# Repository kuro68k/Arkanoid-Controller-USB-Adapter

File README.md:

# Arkanoid-Controller-USB-Adapter

Adapter for the Famicom Arkanoid controller to USB.

Two modes are available, an absolute position mode that is good for Breakout under MAME, and a mouse emulation mode that is better for Arkanoid under MAME.

You need a decent USB port for this. If there is electrical noise it can cause the position to jump. I use a powered hub.

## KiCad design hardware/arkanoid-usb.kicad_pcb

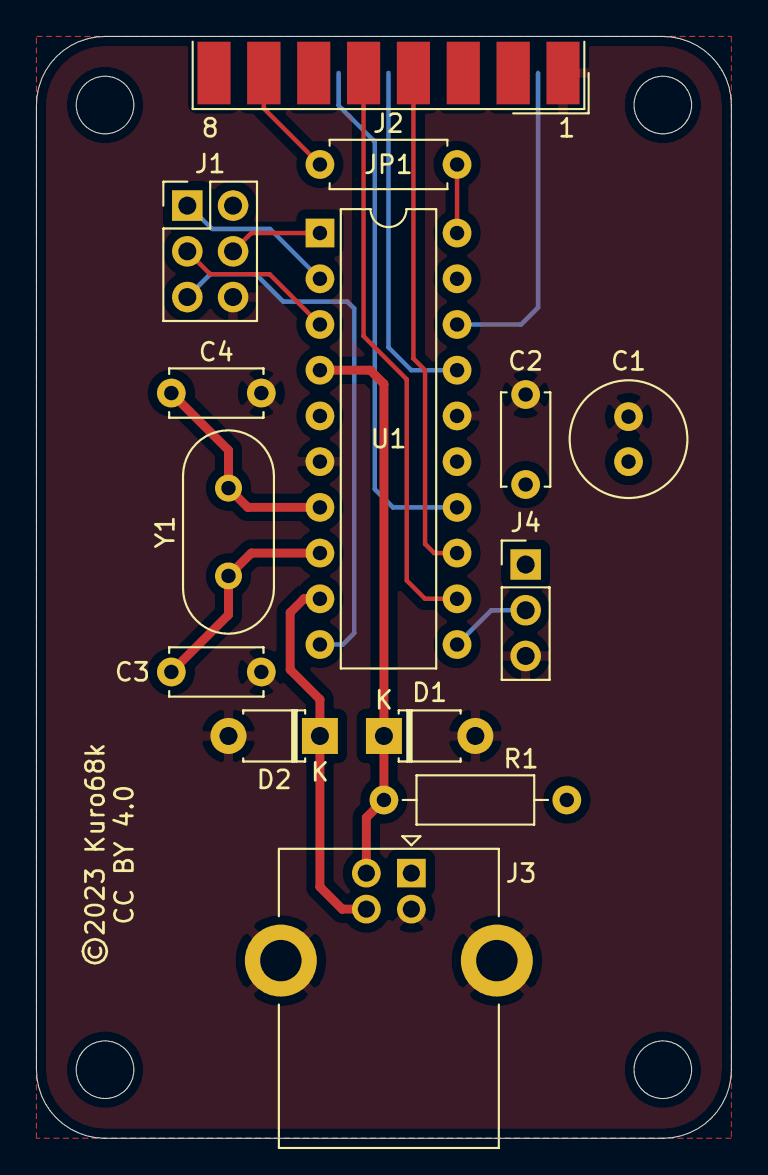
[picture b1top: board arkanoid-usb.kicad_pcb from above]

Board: 2 copper layers, 38.6 x 61.2 mm, 18 parts (0 on the bottom side), 18 nets.

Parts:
C1: 10u; C_Radial_D6.3mm_H5.0mm_P2.50mm
C2: 100n; C_Disc_D5.0mm_W2.5mm_P5.00mm
C3, C4: C; C_Disc_D5.0mm_W2.5mm_P5.00mm
D1, D2: 3V6; D_T-1_P5.08mm_Horizontal
H1, H2, H3, H4: MountingHole; MountingHole_3.2mm_M3
J1: AVR-ISP-6; PinHeader_2x03_P2.54mm_Vertical
J2: Conn_01x15; DSUB-15_Male_EdgeMount_P2.77mm
J3: USB_B; USB_B_Lumberg_2411_02_Horizontal
J4: Conn_01x03; PinHeader_1x03_P2.54mm_Vertical
JP1: Jumper_2_Bridged; R_Axial_DIN0207_L6.3mm_D2.5mm_P7.62mm_Horizontal
R1: 1k5; R_Axial_DIN0207_L6.3mm_D2.5mm_P10.16mm_Horizontal
U1: ATtiny861-20PU; DIP-20_W7.62mm
Y1: 20MHz; Crystal_HC49-U_Vertical

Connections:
+5V: C1.1, C2.1, J1.2, J2.15, J3.1, J4.1, R1.1, U1.5, U1.15
/BUTTON1: J2.13, U1.14
/BUTTON2: J2.5, U1.12
/CLOCK: J2.9, U1.18
/DATA1: JP1.1, U1.20
/DATA2: J2.4, U1.13
/DM: D1.1, J3.2, R1.2, U1.4
/DP: D2.1, J3.3, U1.9
/MISO: J1.1, U1.2
/MOSI: J1.4, U1.1
/POT: J4.2, U1.11
/READ: J2.12, U1.17
/RST: J1.5, U1.10
/SCK: J1.3, U1.3
GND: C1.2, C2.2, C3.2, C4.2, D1.2, D2.2, J1.6, J2.1, J3.4, J3.5, J4.3, U1.6, U1.16
unnamed: C3.1, U1.8, Y1.1
unnamed: C4.1, U1.7, Y1.2
unnamed: J2.7, JP1.2

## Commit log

2023-02-05 Initial code
2023-02-16 Working with Arkanoid II controller
2023-02-19 Auto calibration
2023-02-26 Corrected programming header

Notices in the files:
hardware/arkanoid-usb.kicad_pcb:
©2023 Kuro68k
CC BY 4.0
